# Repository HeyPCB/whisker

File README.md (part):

# Whisker

A drop-in controller for Petoi's Nybble robot cat that runs the stock OpenCat firmware, with USB-C, a 3 A buck and a protected battery input.

Part of [HeyPCB's open robot boards](https://github.com/HeyPCB). Designed end to end with the HeyPCB method on
KiCad 10 (headless pipeline, Freerouting 2.4.1); every number below is measured on the files in this repository.
Mentions of `./run.sh`, `docs/rules/`, `blocks/` or `parts/` refer to the heypcb-kicad SDK that produced them.

| Layers | Outline | Parts | Nets | Connections routed | Vias | ERC errors | DRC errors / unconnected / parity |
|---|---|---|---|---|---|---|---|
| 4 | 64.8 x 55.4 mm | 118 | 81 | 297 -> 0 open | 118 | 0 | 0 / 0 / 0 |

**Not fabricated, assembled or powered.**

| | |
|---|---|
| KiCad project | [`kicad/`](kicad/) |
| Gerbers (unzipped and zipped), BOM, CPL, STEP, schematic PDF | [`fab/`](fab/) |
| Printed parts (STEP/STL), CadQuery source, fit report | [`cad/`](cad/) |
| Renders | [top](media/top.png), [bottom](media/bottom.png) |
| Design process, every step as KiCad rendered it | [`media/design-process.mp4`](media/design-process.mp4) |

Whisker is a controller board for Petoi's Nybble robot cat. It is meant to drop in where the
stock NyBoard V1_2 sits: the same 58.0 x 49.0 mm hole pattern, the same outline with its top
notch, the servo headers at the stock grid on the back. It is **compatible with the Petoi Nybble /
OpenCat firmware** and needs no firmware change: an ATmega328P at 16 MHz and 5 V with the Uno
bootloader, a PCA9685 at 0x40, an MPU-6050 at 0x68 and a 64 Kbit EEPROM at 0x54, every peripheral
on the MCU pin the `NyBoard_V1_2` build expects. Whisker is an independent design. It is not a
Petoi product, and no Petoi schematic, layout or artwork was used.

It was designed with the HeyPCB method on KiCad 10. The headless heypcb-kicad pipeline (KiCad
10.0.6, Freerouting 2.4.1) built it from the brief in `board.json`. The facts it rests on (pin
map, addresses, servo channels, hole pattern, outline, connector positions) come from the
research spec `robots/research/cat/spec.md`, which cites the OpenCat sources and the photo and
STL measurements behind each one.

**This board has not been fabricated, assembled or powered, and it has not run the firmware.**
Firmware compatibility rests on the pin map below, not on a test. Every gate number here is read
from `report.json` of the final run (2026-10-02). Copper, edge and pour figures were
read from `kicad/whisker.kicad_pcb` with KiCad's pcbnew. Fit figures are read from
`cad/fit.json`.

## What it is

- **MCU:** ATmega328P-AU (TQFP-32) with a 16 MHz crystal, 5 V. AVCC sits behind a ferrite, because AVCC is the reference for the battery reading. There is a reset button at the rear edge and a 2x3 ICSP header for burning the Uno (Optiboot) bootloader once.
- **Servos:** a PCA9685PW at I2C 0x40 (all address pins low, OE low, internal oscillator). It drives the 11 Nybble joints on their firmware channels, each through 1k. The ports are 3-row right-angle headers on the back at the stock grid, with GND toward the board edge. Each header group has 10 uF on the rail.
- **IMU and storage:** an MPU-6050 at 0x68, turned 180 degrees like the stock part, with INT on D2. An AT24C64D EEPROM at 0x54 holds the skills.
- **I2C:** a PCA9306 joins the 5 V MCU bus to the 3.3 V bus (the PCA9685, MPU-6050, EEPROM, Grove G1 and the Pi header). There are 2.2k pull-ups on each side for the firmware's 500 kHz clock. A solder jumper, PI I2C, lets the MCU release the bus to a Raspberry Pi.
- **USB-C:** a CH340C behind a USBLC6-2SC6, with DTR auto-reset through 100 nF. The CH340C's TXD reaches RX through 1k, so a dongle can still drive RX.
- **6-pin socket:** kept for the BT and WiFi dongles, in the Pro Mini order (DTR, TX, RX, 5V, NC, GND), with its own DTR auto-reset. It is a vertical 1x6 socket; the stock one lies flat (see *Departures*).
- **Battery input:** a keyed JST XH socket on the back for the 2S pack. An AON6411 P-FET blocks a reversed pack for the whole board, servo rail included. An SMAJ10A clamps the protected rail. The servo rail VBAT has 2 x 330 uF low-ESR electrolytics and 4 x 10 uF ceramics.
- **5 V:** a TPS563201 synchronous buck (3 A) fed from VBAT through an SS34, with a 4.7 uH inductor and an 82k / 15k divider: 0.768 V x (1 + 82/15) = 4.97 V. TI's 5 V table (SLVSD90B Table 7-2) gives 54.9k / 10k; 82k and 15k are both pinned Basic parts.
- **USB power:** USB reaches the 5 V rail only, through a 500 mA PTC and an LM66100 ideal diode (CE on its own output). If the buck's body diode back-feeds its input from USB, the SS34 stops it, so USB never powers the servos.
- **3.3 V:** an XC6206 LDO off 5 V.
- **Peripherals:**
  - a 12 x 12 mm piezo on D5 (tone()), through 100 ohm;
  - an IRM-H638T 38 kHz receiver on D4;
  - a green LED on D3;
  - one WS2812B on D10;
  - blue 5 V and orange servo-rail LEDs;
  - battery sense on A7 through a 20k / 20k divider (the firmware's 1:2).
- **Grove:** four HY2.0 (Grove-compatible) sockets on the front edge:
  - G1: I2C, 3.3 V logic;
  - G2: A2 / A3;
  - G3: D8 / D9;
  - G4: D6 / D7.
- **Raspberry Pi:** a 2x5 socket where a face-to-face Pi's pins 1-10 land.
  - 5 V and GND;
  - SDA and SCL on the 3.3 V bus;
  - the Pi's TXD to RX through 1k;
  - TX to the Pi's RXD through a 1k / 2k divider;
  - GPIO4 to RESET through 100 nF.
- **Board:** 4 layers, 64.6 x 55.2 mm, 1.6 mm thick in the gerber job. The stackup is:
  - F.Cu, signals and a GND pour;
  - In1, signals and a 5 V pour;
  - In2, signals and a VBAT pour;
  - B.Cu, poured GND. It carries 132 mm of track, so it is almost a solid plane.

  There is no plane while routing; see *Departures from the spec*.

## Firmware pin map

The MCU pins, read back from the run's netlist (`design.json`). Firmware sources are listed in the spec, section 1.4.

| ATmega328P pin | Arduino | Net | Function (OpenCat `NyBoard_V1_2`) |
|---|---|---|---|
| 30 / 31 | D0 / D1 | RXD / TXD | serial, 115200 Bd: CH340C (RX through 1k), the 6-pin socket, the Pi (RX through 1k, TX through a divider) |
| 32 | D2 | IMU_INT | MPU-6050 INT (wired; the firmware leaves it unused) |
| 1 | D3 | LED_D3 | green status LED (`LED_PIN 3`) |
| 2 | D4 | IR | IR receiver (`IR_PIN 4`) |
| 9 | D5 | BUZZER | piezo (`BUZZER 5`, tone()) |
| 10 / 11 | D6 / D7 | D6 / D7 | Grove G4 |
| 12 / 13 | D8 / D9 | D8 / D9 | Grove G3 |
| 14 | D10 | NEOPIXEL | WS2812B data, through 330 ohm |
| 15 / 16 / 17 | D11 / D12 / D13 | MOSI / MISO / SCK | ICSP |
| 25 / 26 | A2 / A3 | A2 / A3 | Grove G2. A3 also reaches PCA9685 channel 3 through the open CAL jumper (`PWM_READ_PIN A3`) |
| 27 / 28 | A4 / A5 | SDA5 / SCL5 | I2C, through the PCA9306 to the 3.3 V bus |
| 22 | A7 | VBAT_SENSE | battery divider, 1:2 (`VOLTAGE_DETECTION_PIN A7`, `LOW_VOLTAGE 650`) |
| 29 | RESET | RESET | 10k pull-up, reset button, ICSP; DTR of the CH340C and of the 6-pin socket, and the Pi's GPIO4, each through 100 nF |
| 23, 24, 19 | A0, A1, A6 | none | unused by the V1 firmware, left open |

| I2C device | Address | How it is set |
|---|---|---|
| PCA9685 | 0x40 (All-Call 0x70 also answers) | A0-A5 grounded |
| MPU-6050 | 0x68 | AD0 grounded |
| AT24C64D | 0x54 | A2 high, A1 and A0 low. Petoi's block diagram says 0x51; the text, the V1_2 silkscreen and the firmware say 0x54, and the spec resolves the conflict that way |

**Servo ports.** The channel map is OpenCat's `pwm_pin[]` for NyBoard V1_x (spec 1.6).

- **Columns:** spec board frame, x toward the head. Whisker puts them on an exact 2.54 mm grid from the photo's first columns: 11.26 / 13.80 / 16.34 / 18.88 on the rear half and 40.90 / 43.44 / 45.98 / 48.52 on the front half. The photo measured 11.26 / 13.79 / 16.32 / 18.85 and 40.90 / 43.45 / 46.00 / 48.55 (spec 1.6), within 0.03 mm.
- **Rows:** PWM is the inner row and GND the row nearest the edge. The lower groups (robot's right) sit at y 23.0 / 20.46 / 17.92; the upper groups (robot's left) at y 33.2 / 35.74 / 38.28. The photo measured 23.0 / 20.45 / 17.9 and 33.2 / 35.7 / 38.25.

| Joint | Name | PCA9685 ch | Group | Column x | Header | Silk (back) |
|---|---|---|---|---|---|---|
| 0 | head pan | 12 | upper front | 48.52 | J16 | PAN |
| 1 | head tilt | 11 | lower front | 48.52 | J14 | TILT |
| 2 | tail | 4 | lower rear | 11.26 | J10 | TAIL |
| 8 | left front shoulder | 14 | upper front | 43.44 | J15 | LF SHLD KNEE |
| 12 | left front knee | 15 | upper front | 40.90 | J15 | (same) |
| 9 | right front shoulder | 9 | lower front | 43.44 | J13 | RF SHLD KNEE |
| 13 | right front knee | 8 | lower front | 40.90 | J13 | (same) |
| 10 | right hind hip | 6 | lower rear | 16.34 | J11 | RH |
| 14 | right hind knee | 7 | lower rear | 18.88 | J11 | (same) |
| 11 | left hind hip | 1 | upper rear | 16.34 | J12 | LH |
| 15 | left hind knee | 0 | upper rear | 18.88 | J12 | (same) |

Channels 2, 3, 5, 10 and 13 are unused on Nybble, and their positions are left empty. Channel 3 can feed A3 for the firmware's oscillator calibration once the CAL jumper is bridged.

## Departures from the spec

| Spec or request | On the board | Why |
|---|---|---|
| DMP3013SFV reverse-polarity FET | AON6411 (C81007), -20 V, DFN-8 at 1.27 mm pitch | The PowerDI3333 land puts the gate pad 0.65 mm from a source pad. A 1.0 mm servo-rail track cannot reach source pins 2 and 3 at 0.2 mm clearance; Freerouting runs without neck-down. |
| Passive buzzer on a 2N7002 (stock), MLT-8530 suggested | PKLCS1212E4001 12 x 12 mm piezo, driven from D5 through 100 ohm | KiCad 10 has no land for the MLT-8530 (spec 6). A piezo is a capacitive load and needs no driver or flyback diode. It is 3 mm tall. |
| WS2812C-2020 on KiCad's WS2812B-2020 symbol, "check the pin-out" (spec 6) | WS2812B 5050 (WS2812B-B/T, C2761795) | The repository's rules bind a part only to the symbol for its own package. The 5050 is the part KiCad's `LED:WS2812B` symbol and land are drawn for (pins 1 VDD, 2 DOUT, 3 VSS, 4 DIN), so no pin-out needs checking. |
| I2C master slide switch, kept (spec 4, item 13) | PI I2C solder jumper | The master is chosen once per build, so copper does it, with no part to source or place on the crowded front. Open (the default) keeps the MCU as master. Bridged, it grounds the PCA9306's EN, so a Pi on the 2x5 drives the bus alone. |
| Pi GPIO4 to RST (spec 1.2; no circuit given) | GPIO4 through 100 nF to RESET | A falling edge resets the MCU, as DTR does. A static level, high or low, does nothing. |
| 1x6 female socket lying flat, opening toward +y (stock, spec 1.7) | vertical 1x6 socket (C40877) on KiCad's `PinSocket_1x06_P2.54mm_Vertical` land, within 0.3 mm of the photo's pin positions | Not matched. A dongle plugged in stands up from the board instead of lying along it; see *Check before ordering*. |
| 3-row x 4 right-angle headers | per group, one 2-column and one 1-column land (or one 2-column): KiCad's straight 2x3 / 1x3 lands, on the back, holding a 3-row right-angle header snapped from a 3x3 (PZ254-3-03-W-2.5-G0) | KiCad 10 has no 3-row right-angle land. Separate 1x3 lands at 2.54 mm overlap courtyards. Omitting the five unused channels leaves a pair plus a single per group. |
| Grove sockets at 10.4 mm pitch, plus a 2.54 mm break-out column | sockets at 7.0 mm pitch with their pins along x; no break-out column | At the stock pitch, KiCad's Grove land's 11.4 mm courtyard overlaps its neighbour. The freed lower-right corner holds the Pi's level-shift parts. An 8 mm pitch was tried, and its route left a GND pin open. |
| Notch at least x 6.5-45.1 (spec 2.7) | notch x 6.4-44.8, floor at y 49.6 | The Pi socket sits at the Pi's own pin positions. Its pads keep the 0.5 mm copper-to-edge clearance only with the notch's right edge at 44.8, 0.1 mm inside the photo's 44.9. |
| In1 as the GND plane (the pipeline's default) | no plane while routing; In1 poured 5 V, In2 VBAT, B.Cu GND afterwards | Freerouting mirrors a back-side part's layers. The servo headers' through-hole pins then reach the router with an In1 shape, and Freerouting never joined same-net pin pairs on them (26 and 30 open). With no plane, 297 connections routed to 0. See `docs/rules/pipeline.md`. |

## Measured gates (final run, 2026-10-02, from `report.json`)

| Gate | Result |
|---|---|
| Composition | 31 block instances of 20 blocks (18 new `whisker_*` blocks and HeyPCB's `gpio_led` and `led_indicator`) give 118 parts, 81 nets and 5 explicit no-connects |
| Part binding (`parts/lcsc_pinned.json`) | 112 of 118 parts bound, 0 unsourced, 0 identity conflicts. Two solder jumpers and four holes have nothing to buy. 54 distinct part numbers: 27 Basic, 27 Extended (about $81 in JLC loading fees) |
| ERC (`kicad-cli sch erc --severity-all`) | 0 errors, 0 warnings |
| Netlist round trip | identical, 81 nets |
| Placement | 118 parts, every one locked by the brief. No same-face courtyard overlap and no through-hole inside a courtyard (checked on the placed board before routing) |
| Routing | 297 → **0 open** on rung 2. Rung 1 left 3 open with fanout and 12 without. Rung 2 narrowed the PWR5 class (5V, VBUS, VBUS_F) to 0.2 mm, and its last-mile router closed the battery pin to FET drain hop and one GND link, both kept by DRC. 1181 tracks, 109 routing vias, 2676.6 mm of track: F.Cu 835.9, In1 874.1, In2 834.7, B.Cu 132.0 |
| Pours (only after a measured 0 open) | GND on F.Cu and B.Cu, 5V on In1, VBAT on In2. 10 stitching vias (119 vias in all). 0 open after the pour, after stitching and at the end |
| Silkscreen | 11 words, 7 pin labels and 4 title lines placed. 1 stitching via displaced, 20 designators seated and 87 hidden |
| DRC (`--severity-all --schematic-parity`, KiCad 10.0.6) | fresh, **0 errors, 0 unconnected, 0 parity**, 4 warnings |
| DFM (`jlcpcb_4layer`) | 0 errors, 1 warning: 422 stock-footprint silk strokes at 0.12 mm, which the fab prints at its 0.15 mm minimum |
| Fab gate | **ready**, no blockers. Four copper gerbers, gerber job `LayerNumber` 4. The JLC CPL corrected 9 rotations |
| Media | 63 3D frames, the raytraced renders and the design-process video (1920 x 1080, 179.2 s, 5375 frames by ffprobe) |

**The 4 DRC warnings:**

- `lib_footprint_mismatch` on J9 (the Pi socket) and J2 (USB-C): the board's copies differ from KiCad's library footprints. These are the two footprints at the board edge, where the silk stage clips footprint silk (7 items clipped in this run).
- `silk_over_copper`: JP1's outline arc touches the back battery socket's pin-2 pad.
- `silk_over_copper`: the WS2812B footprint's "1" touches C37's rail pad.

## Copper and power paths

Read from the final `.kicad_pcb` with pcbnew. Current figures use heypcb-kicad's `route.ipc2221_amps` at a 10 C rise. The vias are rated as a 25 um barrel, the way the Spinner README rates its own.

- **Battery feed (BAT_RAW, pack to FET drain): 6.5 mm on F.Cu, 1.5-2.0 mm wide, no via.** The FET's drain pad sits 0.7 mm below the battery pin, so the hop is about 2 mm long.
  - 2.0 mm of 1 oz outer copper carries about 3.9 A; 1.5 mm carries about 3.2 A.
  - The class has `currentA` 5, so the ladder may not narrow it.
- **Servo rail (VBAT): 1.0 mm tracks** with three 0.8 / 0.4 mm vias:
  - F.Cu 48.5 mm, In1 58.6 mm, In2 25.4 mm, B.Cu 16.5 mm;
  - plus the In2 VBAT pour (1963.4 mm² after fill, 8 islands).
  - 1.0 mm is about 2.4 A on 1 oz outer copper, 1.2 A on 1 oz inner and 0.7 A on 0.5 oz inner. A 0.4 mm via is about 2.2 A.
  - The pack's stated peak is 5 A and its typical draw 2 A (spec 3.2). Where the rail runs as a track rather than inside the In2 pour, a 5 A stall peak exceeds the track rating; see *Check before ordering*.
- **5 V: 0.2 mm tracks** (the class narrowed by the ladder), 11 vias:
  - F.Cu 61.2, In1 79.4, In2 116.5, B.Cu 11.0 mm;
  - plus the In1 5 V pour (2055.4 mm², 8 islands), which reaches the Pi socket's 5 V pads, the Grove, ICSP and dongle 5 V pins.
  - The Pi's 5 V pins are on the socket's outer row, against the lobe edge. Between the inner-row pads (0.84 mm gaps) and the edge, only a track of about 0.24 mm, or a pour neck, gets to them. So a Pi can draw far less than the buck's 3 A here; see *Check before ordering*.
- **Buck:** VBUCK and the switch node are 0.6 mm (about 1.65 A on 1 oz outer copper per track), each with two vias.
- **Ground:** B.Cu is one 2584.3 mm² island of GND around 132 mm of track. The F.Cu GND pour is 1975.9 mm² in 7 islands.
- **Edges:** the nearest bodies to the outline are:
  - the USB-C shell, 0.6 mm proud of the rear edge by design;
  - the Pi socket, 0.04 mm inside the notch edge at the Pi's pin positions;
  - L1, 0.65 mm;
  - the piezo, 0.85 mm.

  Every other body is at least 0.95 mm inside the photo-measured outline, which is uncertain by +-0.5 mm.

## Silkscreen

- **Front:**
  - G1 I2C above the first Grove socket and G4 below the last;
  - PI beside the Raspberry Pi socket;
  - the dongle socket's 5V, RX and TX names.
- **Back:**
  - each servo group's joints: TAIL, RH, LH, RF SHLD KNEE, LF SHLD KNEE, PAN, TILT;
  - BATT 2S;
  - the dongle socket's NC, 5V, RX and TX;
  - the title "Whisker", "Nybble / OpenCat compatible", "rev A heypcb-kicad", "not fabricated".
- **Words that found no spot:** the front is packed. USB, RESET, ICSP, G2, G3, IR, the LED names, the two jumpers and the ICs found no free spot on any ring the silk stage tries (each candidate was tested before the brief was settled), so the brief does not ask for them. The LEDs are told apart by colour: orange is the servo rail, blue is 5 V, green is D3. The dongle socket's DTR and GND names landed on neither face.

## The printed cradle (`cad/mount.py`)

A tray that clamps Whisker to Nybble's y1 rails and guards the parts on its back.

- **Geometry:** four 7 mm bosses (the seat the spec asks for), bored 2.4 mm and counterbored underneath. They stand on a 2 mm floor whose top sits 10.5 mm below the board. That clears every body on the back by at least 2 mm: the lowest is the right-angle servo header envelope, at 8.02 mm.
- **Floor outline:** the board polygon inset 1 mm, cut open under the battery socket for its plug and cable, with a window under the PCA9685 and stiffening lips along the two short ends. Nothing stands at the long edges, where the servo plugs leave sideways.
- **Fastening:** an M2 self-tapping screw, about 16 mm, goes up through boss, board and into the y1 pilot hole (Petoi's screw B also fits the bore). The board is clamped between the rail bosses and the cradle.
- **Inputs:** `mount.py` reads the board's real STEP (`fab/whisker.step`, by reference designator), its footprints through pcbnew, and the frame facts of the spec (sections 2.3-2.6 and 5).
- **Output:** 7379.5 mm³, about 9.4 g in PETG. The STL is watertight (trimesh).

Fit, measured with OpenCascade's `BRepExtrema_DistShapeShape` (`cad/fit.json`):

| Pair | Minimum | Note |
|---|---|---|
| Cradle to every body below the board (11 parts) | **1.22 mm** (J9's pin tails), 1.50 mm (J8's) | the servo header envelopes are 2.48 mm above the floor; no interference |
| Cradle to the mated servo plugs | 2.48 mm | plugs above the floor; they leave past the board's long edges |
| Cradle to the battery plug | 1.50 mm | around the floor opening |
| Cradle to the board body | 0 (contact) | only at the four boss seats (136 mm²); common volume 0.0 mm³ |
| Rails (rebuilt) to the board's top-side bodies (105 parts) | **0.10 mm** (J9), 0.20 mm (C20), 0.68 mm (Y1), 0.93 mm (L1) | each is 3.6-10.2 mm from a hole centre, outside the 7 mm seat; the near ones meet the rebuilt boss, not the seat |
| Rails to the cradle | 1.51 mm | the board lies between them |
| Cradle to the belly (rebuilt) | 4.39 mm | lowest board part 8.87 mm, battery plug housing 4.81 mm |

**What these numbers rest on:**

- **Rebuilt, not measured, robot frame.** The spec's STL measurements give:
  - y1 rails 3 mm thick, inner edge X = 28, narrow section X = 28-34.5;
  - bosses reaching in to X = 22.5;
  - 1.4 mm pilot holes at X = +-24.52, Z = +-29 / +-41;
  - an 18.4 mm gap from y1 down to the belly.

  The STLs carry no licence and are not used here. The boss outline is this script's guess: a 7 mm disc plus a bridge to the rail, cut at X = 22.5. The belly gap rests on the spec's shared-frame assumption.
- **Envelopes for parts with no STEP model:**
  - the 3-row right-angle headers (from the PZ254-3-03-W-2.5-G0 catalogue row: 2.54 mm pitch, 2.5 mm insulator, 6 mm pins; standoff and bend gap estimated), which replace the lands' straight-header models;
  - servo plugs 14 mm long (spec 5, estimated);
  - the battery plug 5 mm below its housing (spec 2.4, estimated);
  - envelopes from catalogue heights or estimates for the Grove sockets, USB-C, piezo, reset switch, IR receiver and MPU-6050.

  `fit.json` lists every assumption.

Previews (CadQuery SVG, converted with rsvg-convert), all in `cad/`:

- `cradle_iso.png` and `cradle_top.png`;
- `board_on_cradle_iso.png` and `board_on_cradle_under.png`;
- `fit_iso.png` (with the rails), `fit_side.png` and `fit_end.png`.

## Check these before ordering

The board passes ERC, the netlist round trip, routing, DRC (errors, unconnected and parity), DFM and the fab gate in KiCad. None of it has been built.

**Fit in the robot**
- **The outline is photo-measured:** +-0.5 mm on edges, +-0.3 mm on spacings, from a NyBoard V1_1 photo scaled by its header pitch (spec 2.1-2.2).
  - The 58.0 x 49.0 mm hole pattern is the solid number; the photo, the STL and the Pi standard agree on it.
  - Measure a real NyBoard's width, both top heights (55.4 vs 56.0 in the photo), the notch (x 6.7-44.9, floor 49.9) and its corner radii before ordering.
  - Whisker's notch runs x 6.4-44.8, which is 0.3 mm narrower on the right than the spec recommends.
- **The y1 bosses.** The Pi socket (0.10 mm) and C20 (0.20 mm) are the closest bodies to the rebuilt rail bosses, whose outline is a guess. Look at the real y1 bosses next to those two parts before ordering.
- **The dongle socket stands upright.** The stock 1x6 socket lies flat with its opening toward the notch, so a plugged dongle rises about 10 mm (spec 2.4). On Whisker the socket is vertical, so a dongle stands up by its own length. Check that it clears the robot's cover, or change J8 to a right-angle socket before ordering.
- **USB-C access** at the tail edge has not been checked against the frame (spec 8). The shell stands 0.6 mm proud of the rear edge.
- **Heights on top:**
  - Grove sockets 8 mm (catalogue row);
  - the dongle and Pi sockets 8.5 mm;
  - the bulk capacitors 7.7 mm.

  The spec estimates the stock board's tallest top part at 6-7 mm. A Pi stacked on the 2x5 sits over the bulk capacitors; that clearance was not checked.
- **The space under the board** (about 16.9 mm from the board to the rebuilt belly) is an estimate from the STLs' shared frame (spec 8, item 2). The cradle leaves 4.39 mm of it.

**Firmware-visible choices**
- **MPU-6050 orientation.** U9 is turned 180 degrees: the spec's reading of the stock board's photo, which it lists as unconfirmed (spec 8, item 3). The firmware applies no axis remapping. Check on a real NyBoard (spec 1.7: print with token `v`, tilt nose-down and left-side-down) and turn U9 to match if it differs.
- **The 6-pin socket's order** follows the V1_1 photo and the Arduino Pro Mini (TX next to DTR, pin 5 NC). Petoi's text lists 2 RX / 3 TX and pin 5 GND. Check against a dongle before plugging one in.
- **The piezo** resonates at 4 kHz and is quieter away from it; OpenCat's melodies sit mostly below 4 kHz. Listen to one before committing to it.
- **I2C at 500 kHz** with 2.2k on each side of the PCA9306: check the rise time with Grove modules on the bus.
- **Crystal load:** 12 pF caps for the X322516MLB4SI's 9 pF load (catalogue row). Check the oscillation margin.

**Current**
- **Servo rail.** The 1.0 mm VBAT tracks rate about 2.4 A on outer copper and 1.2 A on 1 oz inner copper. The In2 pour carries the rest between the header groups. All eleven servos stalling at once draw up to the pack's 5 A. Widen the F.Cu and In1 VBAT runs between the bulk capacitors and the groups if the robot runs hard, and choose 1 oz inner copper when ordering.
- **5 V for a Pi.** The buck delivers 3 A, but the 5 V copper is 0.2 mm tracks and the In1 pour, and the Pi's 5 V pins are reachable only through 0.84 mm gaps between the socket's inner-row pads. A Pi 3A+ at its typical draw is plausible; a heavier Pi is not supported. With USB alone, the 500 mA PTC cannot power a Pi.
- **Reverse polarity.** The AON6411's gate sees -8.4 V from a full 2S pack. One LCSC listing of the same MPN (C52205210) gives +-12 V for it; check AOS's datasheet.
- **The TVS (SMAJ10A)** stands off 10 V and clamps at 17 V (catalogue row), under the AON6411's 20 V.

**Parts and assembly**
- **Servo headers.** Fit a 3-row right-angle header snapped from a 3x3 (PZ254-3-03-W-2.5-G0) into each land from the back, pins pointing out toward the robot's side, GND row outermost. The lands are KiCad's straight 2x3 / 1x3, and the 3D renders show their straight-pin models. The cradle fit check uses the right-angle envelope instead.
- **Grove.** The ZX-HY2.0-4PZZ sits on KiCad's NS-Tech Grove land. Its pins and pegs were not checked against the ZX drawing.
- **Missing 3D models.** KiCad 10.0.6 installs no 3D model for the Grove land, the IRM-H6xxT, the piezo, the reset switch or the MPU-6050 QFN. The renders show them as lands only. The IR receiver's lens direction is not recorded here; check that it looks out of the rear edge.
- **MPU-6050.** It is obsolete / NRND at TDK (spec 4). Buy the build quantity now.
- **Part numbers and stock.**
  - Every part number in `fab/whisker_bom.csv` comes from `parts/lcsc_pinned.json`: 29 rows were looked up live on 2026-10-02 and the rest are older pinned rows (2026-06-23 to 2026-09-30).
  - The lowest stock is the AON6411 (2346), then the PCA9685 (2772) and the right-angle header (3559).
  - Stock and Basic/Extended class change daily; re-check before ordering.
- **Stackup.** The gerber job lists KiCad's default 4-layer stackup: 35 um copper and 0.48 mm FR4 x 3. Choose the inner copper weight when ordering.

## Licence and attribution

- **OpenCat firmware.** OpenCat (github.com/PetoiCamp/OpenCat-Quadruped-Robot) is MIT-licensed: "Copyright (c) 2022 Rongzhong Li" and Petoi LLC. Whisker contains none of its code. The pin map, I2C addresses and servo channel map above are facts read from it and cited in the research spec. Keep OpenCat's copyright and permission notice when redistributing the firmware for this board.
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
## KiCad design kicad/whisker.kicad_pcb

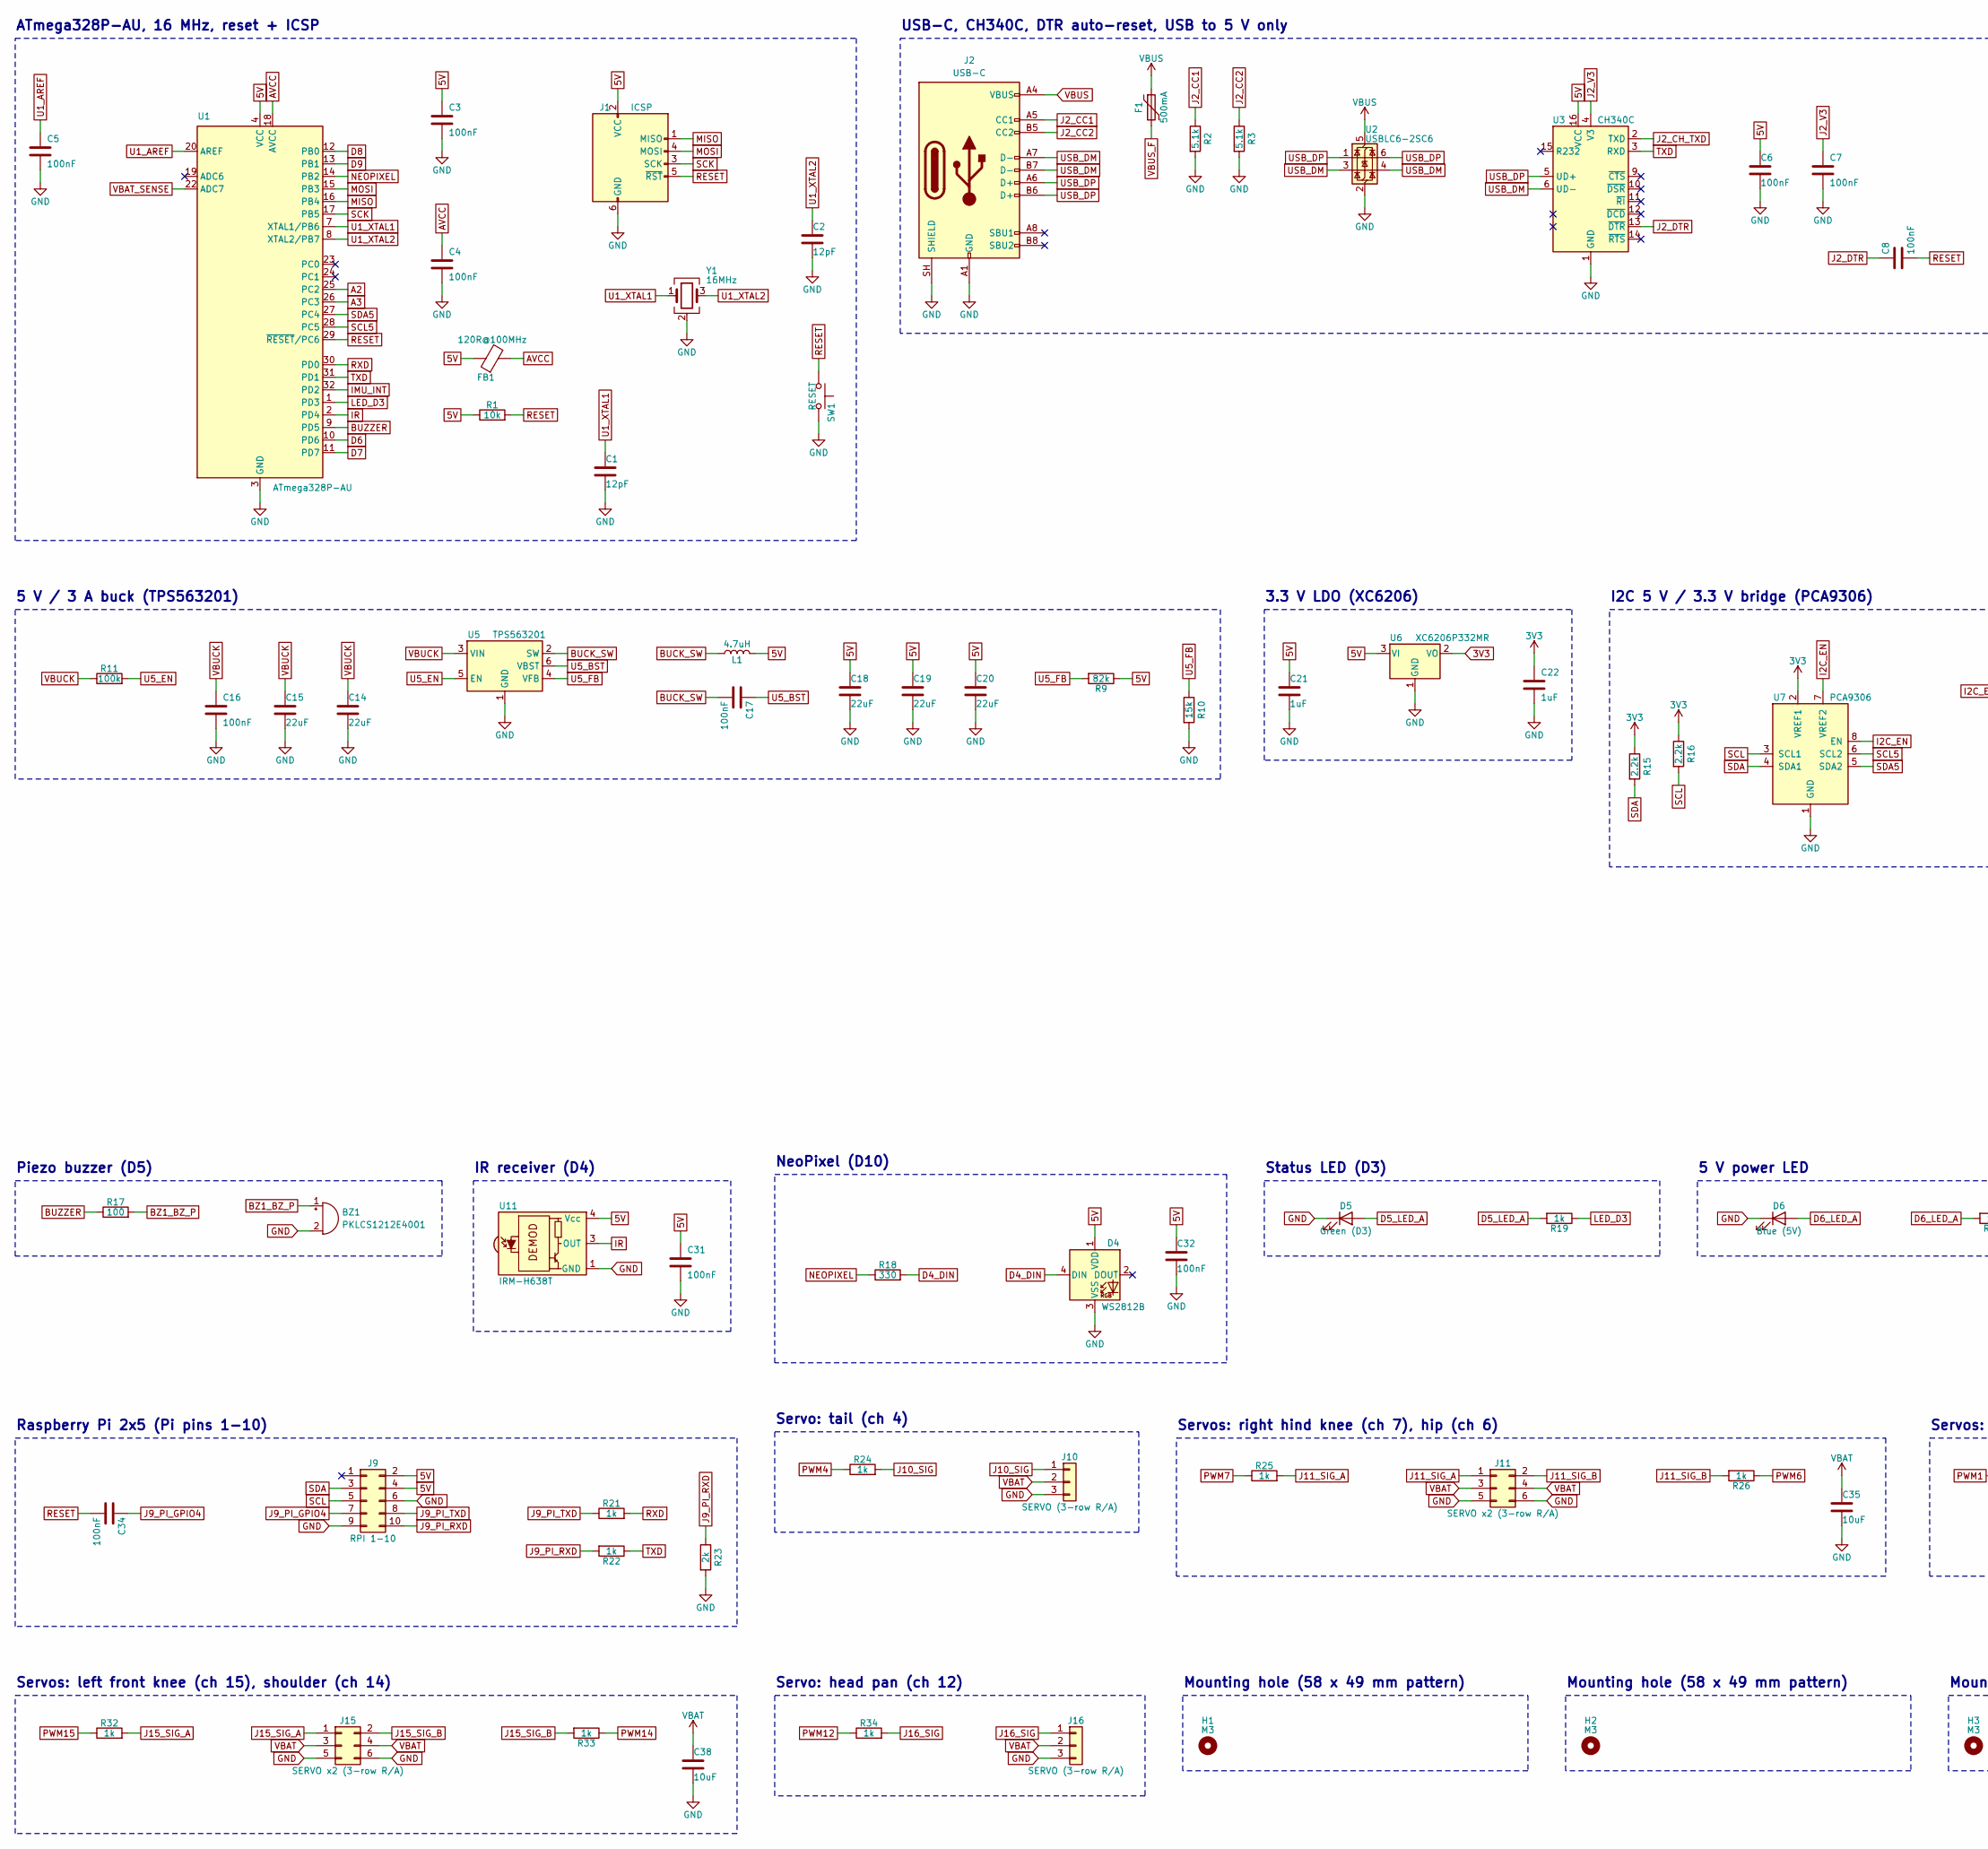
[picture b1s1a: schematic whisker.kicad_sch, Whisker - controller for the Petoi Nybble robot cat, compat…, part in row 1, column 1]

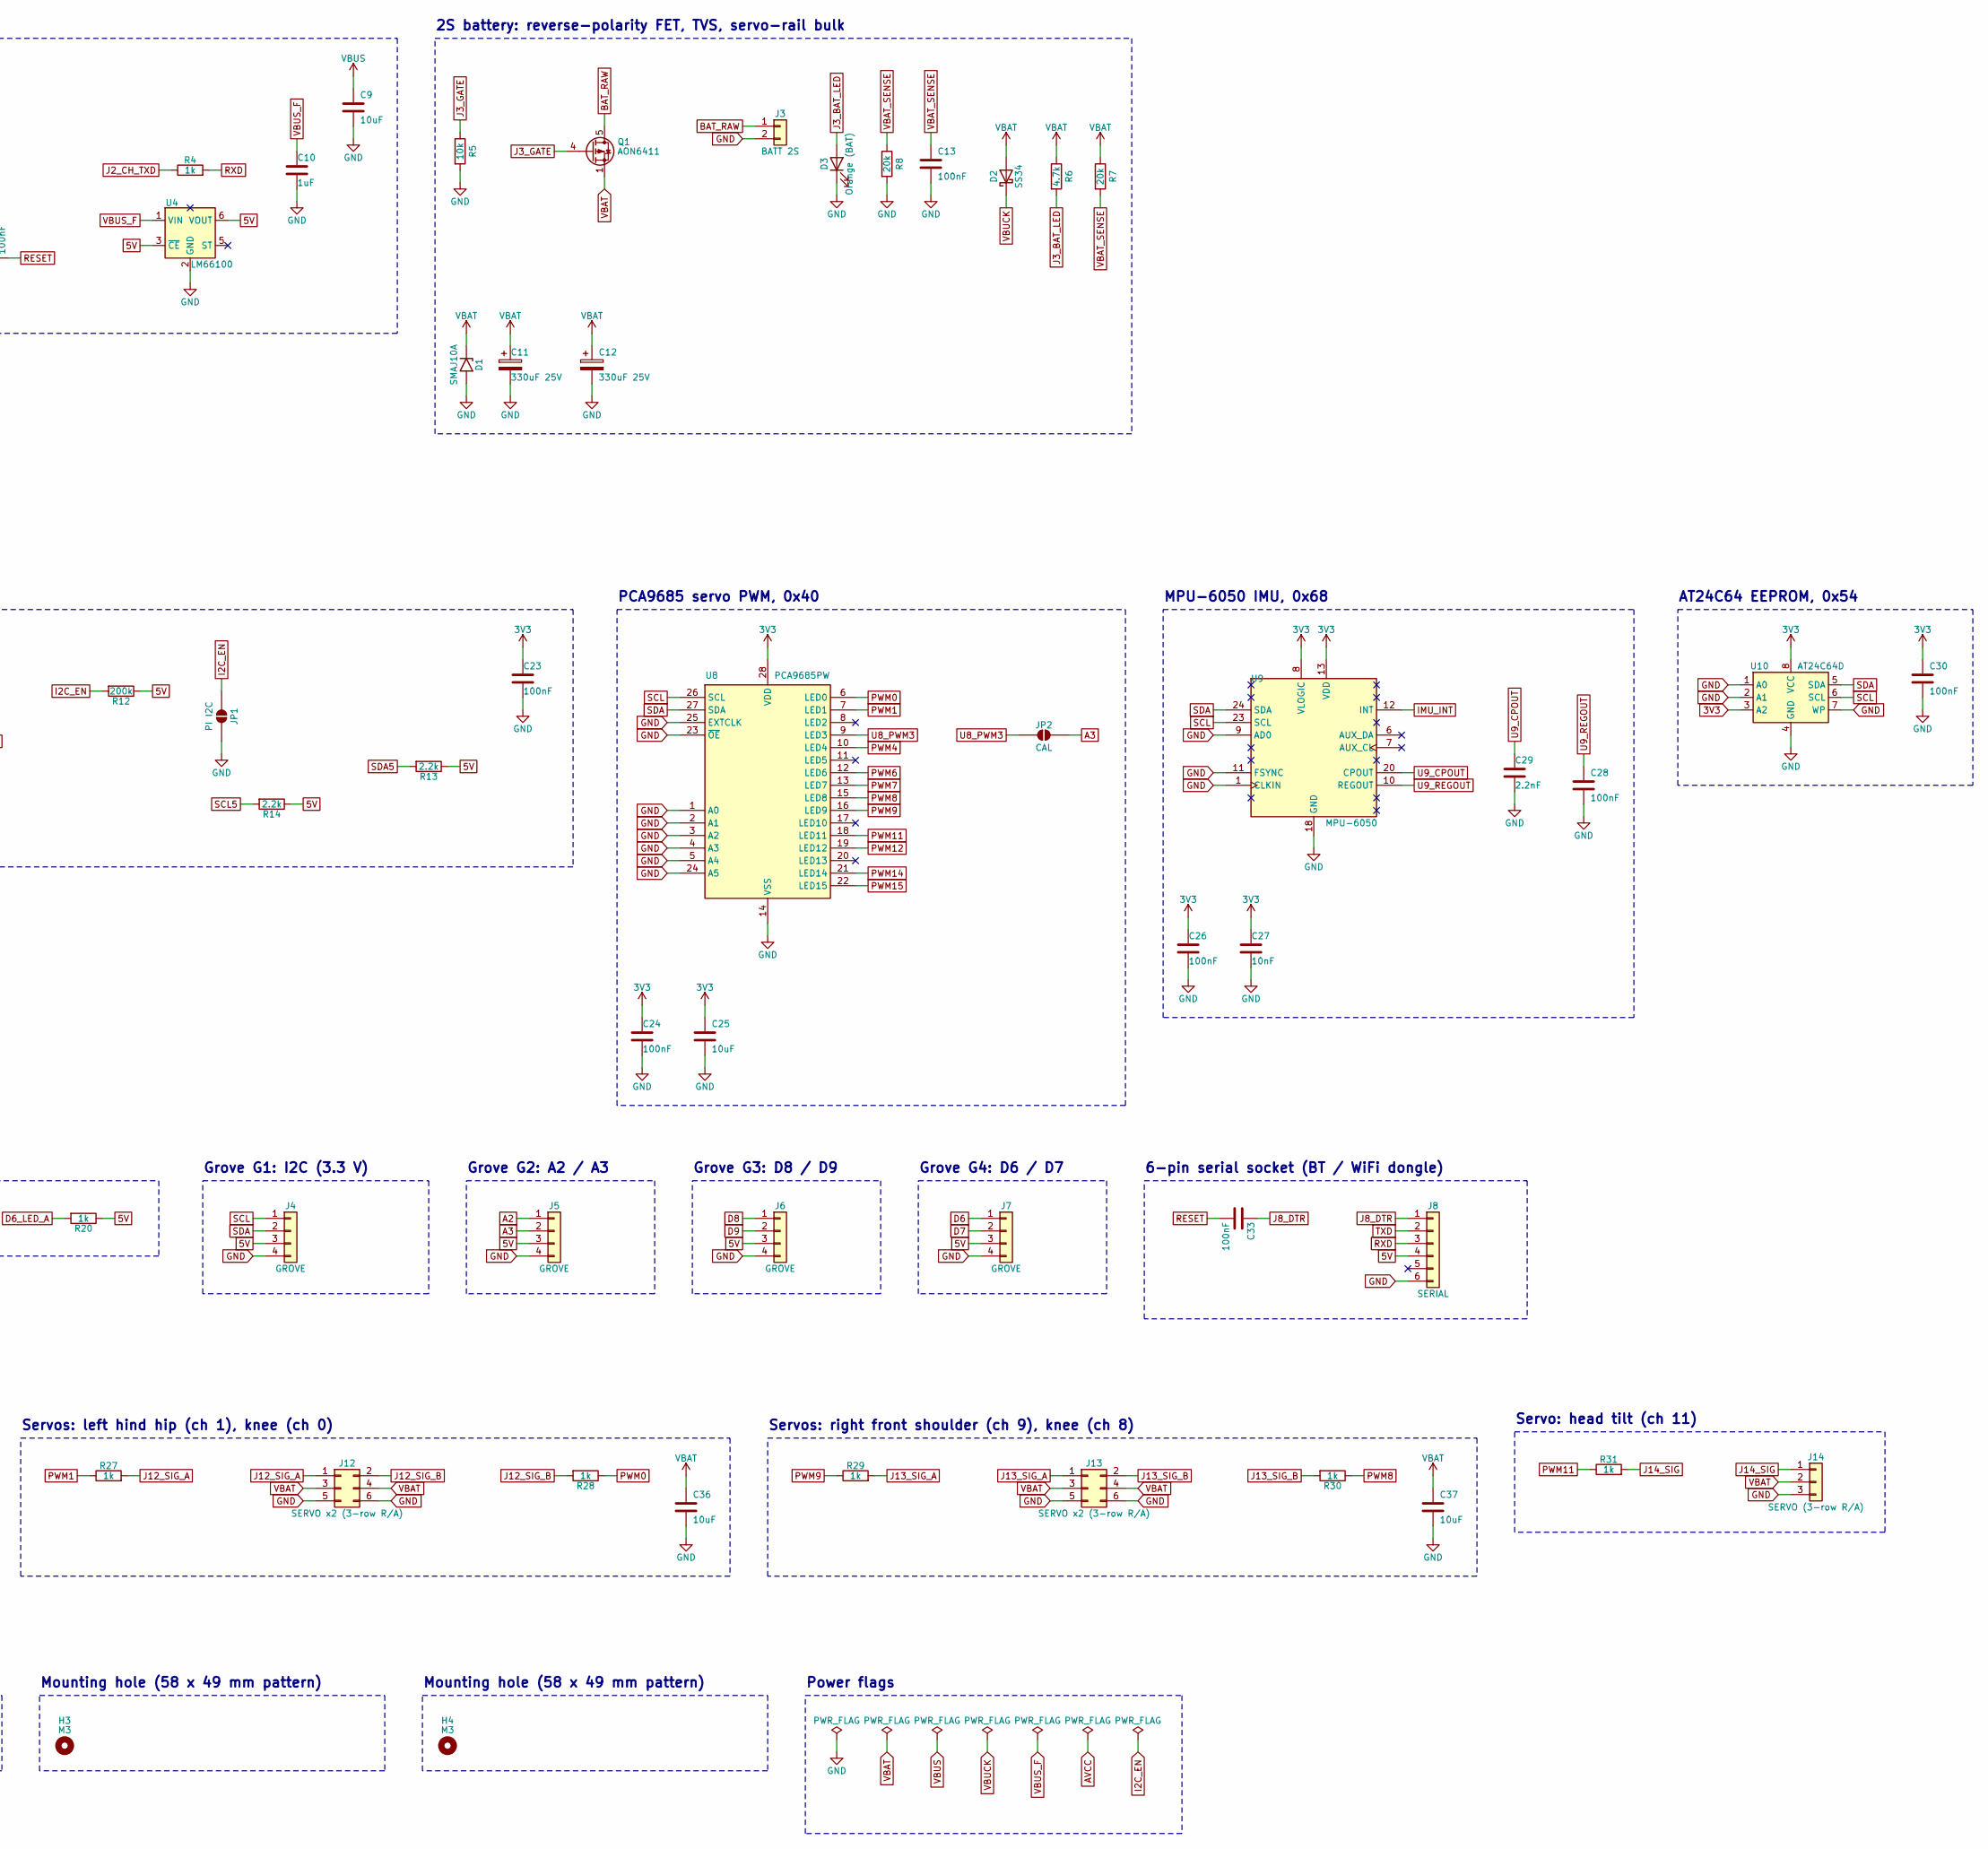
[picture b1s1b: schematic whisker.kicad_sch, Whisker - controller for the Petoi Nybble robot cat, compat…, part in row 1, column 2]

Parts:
BZ1: PKLCS1212E4001; Buzzer_Murata_PKLCS1212E; MPN PKLCS1212E4001-R1; LCSC C113159
C1, C2: 12pF; C_0603_1608Metric; MPN CL10C120JB8NNNC; LCSC C38523
C3, C6, C7, C8, C16, C17, C23, C24, C31, C32, C33, C34: 100nF; C_0603_1608Metric; MPN CC0603KRX7R9BB104; LCSC C14663
C4, C5, C13, C26, C28, C30: 100nF; C_0402_1005Metric; MPN CL05B104KO5NNNC; LCSC C1525
C9, C25: 10uF; C_0805_2012Metric; MPN CL21A106KAYNNNE; LCSC C15850
C10, C21, C22: 1uF; C_0603_1608Metric; MPN CL10A105KB8NNNC; LCSC C15849
C11, C12: 330uF 25V; CP_Elec_6.3x7.7; MPN 189RV0016; LCSC C7471878
C14, C15, C18, C19, C20: 22uF; C_0805_2012Metric; MPN CL21A226MAQNNNE; LCSC C45783
C27: 10nF; C_0402_1005Metric; MPN CL05B103KB5NNNC; LCSC C15195
C29: 2.2nF; C_0603_1608Metric; MPN 0603B222K500NT; LCSC C1604
C35, C36, C37, C38: 10uF; C_1206_3216Metric; MPN CL31A106KBHNNNE; LCSC C13585
D1: SMAJ10A; D_SMA; MPN SMAJ10A; LCSC C908764
D2: SS34; D_SMA; MPN SS34; LCSC C8678
D3: Orange (BAT); LED_0603_1608Metric; MPN XL-1608UOC-06; LCSC C965800
D4: WS2812B; LED_WS2812B_PLCC4_5.0x5.0mm_P3.2mm; MPN WS2812B-B/T; LCSC C2761795
D5: Green (D3); LED_0603_1608Metric; MPN KT-0603G; LCSC C12624
D6: Blue (5V); LED_0603_1608Metric; MPN NCD0603B1; LCSC C84266
F1: 500mA; Fuse_1206_3216Metric; MPN 1206L050/30NR; LCSC C7542947
FB1: 120R@100MHz; L_0603_1608Metric; MPN BLM18PG121SN1D; LCSC C14709
H1, H2, H3, H4: M3; MountingHole_3.2mm_M3_ISO14580
J1: ICSP; PinHeader_2x03_P2.54mm_Vertical; MPN PZ254V-12-6P; LCSC C492420
J2: USB-C; USB_C_Receptacle_HRO_TYPE-C-31-M-12; MPN TYPE-C-31-M-12; LCSC C165948
J3: BATT 2S; JST_XH_B2B-XH-A_1x02_P2.50mm_Vertical; MPN B2B-XH-A(LF)(SN); LCSC C158012
J4, J5, J6, J7: GROVE; NS-Tech_Grove_1x04_P2mm_Vertical; MPN ZX-HY2.0-4PZZ; LCSC C7429580
J8: SERIAL; PinSocket_1x06_P2.54mm_Vertical; MPN 2.54-1*6P母; LCSC C40877
J9: RPI 1-10; PinSocket_2x05_P2.54mm_Vertical; MPN PM254V-12-10P-H85; LCSC C492399
J10, J14, J16: SERVO (3-row R/A); PinHeader_1x03_P2.54mm_Vertical; MPN PZ254-3-03-W-2.5-G0; LCSC C7429379
J11, J12, J13, J15: SERVO x2 (3-row R/A); PinHeader_2x03_P2.54mm_Vertical; MPN PZ254-3-03-W-2.5-G0; LCSC C7429379
JP1: PI I2C; SolderJumper-2_P1.3mm_Open_RoundedPad1.0x1.5mm
JP2: CAL; SolderJumper-2_P1.3mm_Open_RoundedPad1.0x1.5mm
L1: 4.7uH; L_Sunlord_SWPA6045S; MPN SWPA6045S4R7MT; LCSC C78804
Q1: AON6411; AO_DFN-8-1EP_5.55x5.2mm_P1.27mm_EP4.12x4.6mm; MPN AON6411; LCSC C81007
R1, R5: 10k; R_0402_1005Metric; MPN 0402WGF1002TCE; LCSC C25744
R2, R3: 5.1k; R_0402_1005Metric; MPN 0402WGF5101TCE; LCSC C25905
R4, R19, R20, R21, R22, R24, R25, R26, R27, R28, R29, R30, R31, R32, R33, R34: 1k; R_0603_1608Metric; MPN 0603WAF1001T5E; LCSC C21190
R6: 4.7k; R_0603_1608Metric; MPN 0603WAF4701T5E; LCSC C23162
R7, R8: 20k; R_0603_1608Metric; MPN 0603WAF2002T5E; LCSC C4184
R9: 82k; R_0603_1608Metric; MPN 0603WAF8202T5E; LCSC C23254
R10: 15k; R_0603_1608Metric; MPN 0603WAF1502T5E; LCSC C22809
R11: 100k; R_0603_1608Metric; MPN 0603WAF1003T5E; LCSC C25803
R12: 200k; R_0603_1608Metric; MPN 0603WAF2003T5E; LCSC C25811
R13, R14, R15, R16: 2.2k; R_0603_1608Metric; MPN 0603WAF2201T5E; LCSC C4190
R17: 100; R_0603_1608Metric; MPN 0603WAF1000T5E; LCSC C22775
R18: 330; R_0603_1608Metric; MPN 0603WAF3300T5E; LCSC C23138
R23: 2k; R_0603_1608Metric; MPN 0603WAF2001T5E; LCSC C22975
SW1: RESET; SW_Push_1P1T_XKB_TS-1187A; MPN TS-1187A-B-A-B; LCSC C318884
U1: ATmega328P-AU; TQFP-32_7x7mm_P0.8mm; MPN ATMEGA328P-AU; LCSC C14877
U2: USBLC6-2SC6; SOT-23-6; MPN USBLC6-2SC6; LCSC C7519
U3: CH340C; SOIC-16_3.9x9.9mm_P1.27mm; MPN CH340C; LCSC C84681
U4: LM66100; SOT-363_SC-70-6; MPN LM66100DCKR; LCSC C2869734
U5: TPS563201; SOT-23-6; MPN TPS563201DDCR; LCSC C116592
U6: XC6206P332MR; SOT-23-3; MPN XC6206P332MR-G; LCSC C5446
U7: PCA9306; VSSOP-8_2.3x2mm_P0.5mm; MPN PCA9306DCUR; LCSC C33196
U8: PCA9685PW; TSSOP-28_4.4x9.7mm_P0.65mm; MPN PCA9685PW,118; LCSC C2678753
U9: MPU-6050; InvenSense_QFN-24_4x4mm_P0.5mm; MPN MPU-6050; LCSC C24112
U10: AT24C64D; SOIC-8_3.9x4.9mm_P1.27mm; MPN AT24C64D-SSHM-T; LCSC C6487
U11: IRM-H638T; Everlight_IRM-H6xxT; MPN IRM-H638T/TR2; LCSC C91447
Y1: 16MHz; Crystal_SMD_3225-4Pin_3.2x2.5mm; MPN X322516MLB4SI; LCSC C13738

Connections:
3V3: C22.1, C23.1, C24.1, C25.1, C26.1, C27.1, C30.1, R15.1, R16.1, U6.2 (VO), U7.2 (VREF1), U8.28 (VDD), U9.8 (VLOGIC), U9.13 (VDD), U10.3 (A2), U10.8 (VCC)
5V: C3.1, C6.1, C18.1, C19.1, C20.1, C21.1, C31.1, C32.1, D4.1 (VDD), FB1.1, J1.2 (VCC), J4.3, J5.3, J6.3, J7.3, J8.4, J9.2, J9.4, L1.2, R1.1, R9.1, R12.1, R13.1, R14.1, R20.1, U1.4 (VCC), U1.6 (VCC), U3.16 (VCC), U4.3 (~CE), U4.6 (VOUT), U6.3 (VI), U11.4 (Vcc)
A2: J5.1, U1.25 (PC2)
A3: J5.2, JP2.2 (B), U1.26 (PC3)
AVCC: C4.1, FB1.2, U1.18 (AVCC)
BAT_RAW: J3.1, Q1.5 (D)
BUCK_SW: C17.2, L1.1, U5.2 (SW)
BUZZER: R17.1, U1.9 (PD5)
BZ1_BZ_P: BZ1.1 (+), R17.2
D4_DIN: D4.4 (DIN), R18.2
D5_LED_A: D5.2 (A), R19.2
D6: J7.1, U1.10 (PD6)
D6_LED_A: D6.2 (A), R20.2
D7: J7.2, U1.11 (PD7)
D8: J6.1, U1.12 (PB0)
D9: J6.2, U1.13 (PB1)
GND: BZ1.2 (-), C1.2, C2.2, C3.2, C4.2, C5.2, C6.2, C7.2, C9.2, C10.2, C11.2, C12.2, C13.2, C14.2, C15.2, C16.2, C18.2, C19.2, C20.2, C21.2, C22.2, C23.2, C24.2, C25.2, C26.2, C27.2, C28.2, C29.2, C30.2, C31.2, C32.2, C35.2, C36.2, C37.2, C38.2, D1.2 (A2), D3.1 (K), D4.3 (VSS), D5.1 (K), D6.1 (K), J1.6 (GND), J2.A1 (GND), J2.A12 (GND), J2.B1 (GND), J2.B12 (GND), J2.SH (SHIELD), J3.2, J4.4, J5.4, J6.4, J7.4, J8.6, J9.6, J9.9, J10.3, J11.5, J11.6, J12.5, J12.6, J13.5, J13.6, J14.3, J15.5, J15.6, J16.3, JP1.2 (B), R2.2, R3.2, R5.2, R8.2, R10.2, R23.2, SW1.2, U1.3 (GND), U1.5 (GND), U1.21 (GND), U2.2 (GND), U3.1 (GND), U4.2 (GND), U5.1 (GND), U6.1 (GND), U7.1 (GND), U8.1 (A0), U8.2 (A1), U8.3 (A2), U8.4 (A3), U8.5 (A4), U8.14 (VSS), U8.23 (~OE), U8.24 (A5), U8.25 (EXTCLK), U9.1 (CLKIN), U9.9 (AD0), U9.11 (FSYNC), U9.18 (GND), U10.1 (A0), U10.2 (A1), U10.4 (GND), U10.7 (WP), U11.1 (GND), U11.2 (GND), Y1.2 (G), Y1.4 (G)
I2C_EN: JP1.1 (A), R12.2, U7.7 (VREF2), U7.8 (EN)
IMU_INT: U1.32 (PD2), U9.12 (INT)
IR: U1.2 (PD4), U11.3 (OUT)
J2_CC1: J2.A5 (CC1), R2.1
J2_CC2: J2.B5 (CC2), R3.1
J2_CH_TXD: R4.1, U3.2 (TXD)
J2_DTR: C8.1, U3.13 (~DTR)
J2_V3: C7.1, U3.4 (V3)
J3_BAT_LED: D3.2 (A), R6.2
J3_GATE: Q1.4 (G), R5.1
J8_DTR: C33.1, J8.1
J9_PI_GPIO4: C34.1, J9.7
J9_PI_RXD: J9.10, R22.2, R23.1
J9_PI_TXD: J9.8, R21.1
J10_SIG: J10.1, R24.2
J11_SIG_A: J11.1, R25.2
J11_SIG_B: J11.2, R26.2
J12_SIG_A: J12.1, R27.2
J12_SIG_B: J12.2, R28.2
J13_SIG_A: J13.1, R29.2
J13_SIG_B: J13.2, R30.2
J14_SIG: J14.1, R31.2
J15_SIG_A: J15.1, R32.2
J15_SIG_B: J15.2, R33.2
J16_SIG: J16.1, R34.2
LED_D3: R19.1, U1.1 (PD3)
MISO: J1.1 (MISO), U1.16 (PB4)
MOSI: J1.4 (MOSI), U1.15 (PB3)
NEOPIXEL: R18.1, U1.14 (PB2)
PWM0: R28.1, U8.6 (LED0)
PWM1: R27.1, U8.7 (LED1)
PWM4: R24.1, U8.10 (LED4)
PWM6: R26.1, U8.12 (LED6)
PWM7: R25.1, U8.13 (LED7)
PWM8: R30.1, U8.15 (LED8)
PWM9: R29.1, U8.16 (LED9)
PWM11: R31.1, U8.18 (LED11)
PWM12: R34.1, U8.19 (LED12)
PWM14: R33.1, U8.21 (LED14)
PWM15: R32.1, U8.22 (LED15)
RESET: C8.2, C33.2, C34.2, J1.5 (~RST), R1.2, SW1.1, U1.29 (~RESET/PC6)
RXD: J8.3, R4.2, R21.2, U1.30 (PD0)
SCK: J1.3 (SCK), U1.17 (PB5)
SCL: J4.1, J9.5, R16.2, U7.3 (SCL1), U8.26 (SCL), U9.23 (SCL), U10.6 (SCL)
SCL5: R14.2, U1.28 (PC5), U7.6 (SCL2)
SDA: J4.2, J9.3, R15.2, U7.4 (SDA1), U8.27 (SDA), U9.24 (SDA), U10.5 (SDA)
SDA5: R13.2, U1.27 (PC4), U7.5 (SDA2)
TXD: J8.2, R22.1, U1.31 (PD1), U3.3 (RXD)
U1_AREF: C5.1, U1.20 (AREF)
U1_XTAL1: C1.1, U1.7 (XTAL1/PB6), Y1.1
U1_XTAL2: C2.1, U1.8 (XTAL2/PB7), Y1.3
U5_BST: C17.1, U5.6 (VBST)
U5_EN: R11.2, U5.5 (EN)
U5_FB: R9.2, R10.1, U5.4 (VFB)
U8_PWM3: JP2.1 (A), U8.9 (LED3)
U9_CPOUT: C29.1, U9.20 (CPOUT)
U9_REGOUT: C28.1, U9.10 (REGOUT)
USB_DM: J2.A7 (D-), J2.B7 (D-), U2.3 (I/O2), U2.4 (I/O2), U3.6 (UD-)
USB_DP: J2.A6 (D+), J2.B6 (D+), U2.1 (I/O1), U2.6 (I/O1), U3.5 (UD+)
VBAT: C11.1, C12.1, C35.1, C36.1, C37.1, C38.1, D1.1 (A1), D2.2 (A), J10.2, J11.3, J11.4, J12.3, J12.4, J13.3, J13.4, J14.2, J15.3, J15.4, J16.2, Q1.1 (S), Q1.2 (S), Q1.3 (S), R6.1, R7.1
VBAT_SENSE: C13.1, R7.2, R8.1, U1.22 (ADC7)
VBUCK: C14.1, C15.1, C16.1, D2.1 (K), R11.1, U5.3 (VIN)
VBUS: C9.1, F1.1, J2.A4 (VBUS), J2.A9 (VBUS), J2.B4 (VBUS), J2.B9 (VBUS), U2.5 (VBUS)
VBUS_F: C10.1, F1.2, U4.1 (VIN)

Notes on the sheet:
ATmega328P-AU, 16 MHz, reset + ICSP
USB-C, CH340C, DTR auto-reset, USB to 5 V only
2S battery: reverse-polarity FET, TVS, servo-rail bulk
5 V / 3 A buck (TPS563201)
3.3 V LDO (XC6206)
I2C 5 V / 3.3 V bridge (PCA9306)
PCA9685 servo PWM, 0x40
MPU-6050 IMU, 0x68
AT24C64 EEPROM, 0x54
Piezo buzzer (D5)
IR receiver (D4)
NeoPixel (D10)
Status LED (D3)
5 V power LED
Grove G1: I2C (3.3 V)
Grove G2: A2 / A3
Grove G3: D8 / D9
Grove G4: D6 / D7
6-pin serial socket (BT / WiFi dongle)
Raspberry Pi 2x5 (Pi pins 1-10)
Servo: tail (ch 4)
Servos: right hind knee (ch 7), hip (ch 6)
Servos: left hind hip (ch 1), knee (ch 0)
Servos: right front shoulder (ch 9), knee (ch 8)
Servo: head tilt (ch 11)
Servos: left front knee (ch 15), shoulder (ch 14)
Servo: head pan (ch 12)
Mounting hole (58 x 49 mm pattern)
Power flags

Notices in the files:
README.md:
- **Petoi hardware.** The NyBoard's schematic, layout and gerbers are not published under any licence. Whisker is therefore an independent, functionally and mechanically compatible design built from facts: the pi
Hardware: [CERN-OHL-S v2](LICENSE). Files under `cad/` that derive from third-party CAD carry their own notice there.
- **KiCad libraries.** The symbols, footprints and 3D models are KiCad's (CC-BY-SA-4.0 with the KiCad library exception). The USB-C body is heypcb-kicad's generated envelope.
